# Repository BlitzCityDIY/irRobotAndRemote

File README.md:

This is for a rover robot built with the Adafruit Crickit board. 

It's controlled with an IR remote using an Adafruit Trinket M0, Adafruit Seesaw and custom PCB.

Coded with CircuitPython.

Project Videos:

https://youtu.be/yoQC8QCEBIY

https://youtu.be/6JI83SIRhTM

https://youtu.be/Heaa0BWK_Mk

https://youtu.be/sYn7sI7BDCw

Fusion 360 Public Links

Remote Main Body: https://a360.co/2XNJTZd

LED Cat Faceplate: https://a360.co/2WIM9Eo

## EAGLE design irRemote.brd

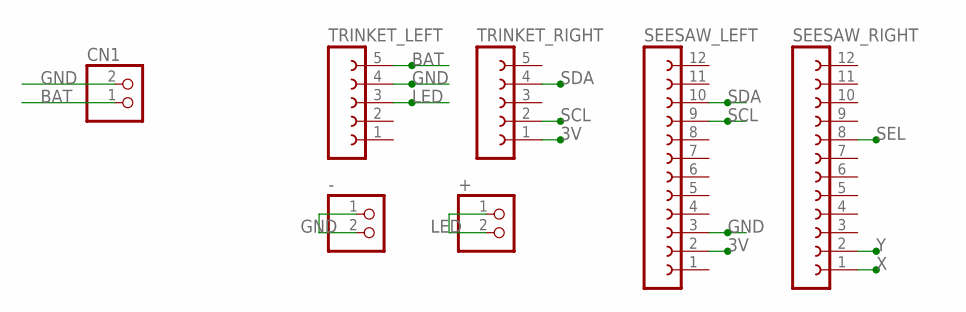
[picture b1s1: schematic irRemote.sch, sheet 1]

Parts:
+: PINHD-1X2; 1X02
-: PINHD-1X2; 1X02
CN1: JST_2PIN-SMT-RA; JST-PH-2-SMT-RA
SEESAW_LEFT: FE12-1; FE12
SEESAW_RIGHT: FE12-1; FE12
TRINKET_LEFT: FE05-1
TRINKET_RIGHT: FE05-1

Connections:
3V: SEESAW_LEFT.2, TRINKET_RIGHT.1; also elsewhere on the board
BAT: CN1.1 (2), TRINKET_LEFT.5
GND: -.1, -.2, CN1.2 (1), SEESAW_LEFT.3, TRINKET_LEFT.4; also elsewhere on the board
LED: +.1, +.2, TRINKET_LEFT.3
SCL: SEESAW_LEFT.9, TRINKET_RIGHT.2
SDA: SEESAW_LEFT.10, TRINKET_RIGHT.4
SEL: SEESAW_RIGHT.8; also elsewhere on the board
X: SEESAW_RIGHT.1; also elsewhere on the board
Y: SEESAW_RIGHT.2; also elsewhere on the board

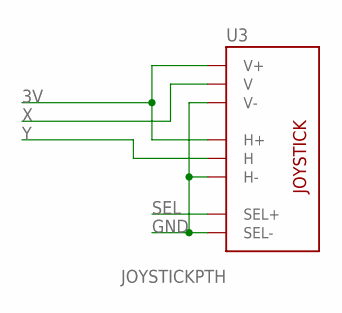
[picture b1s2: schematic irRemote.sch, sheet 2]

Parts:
U3: JOYSTICKPTH; JOYSTICK

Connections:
3V: U3.H1 (H+), U3.V1 (V+); also elsewhere on the board
GND: U3.B2A (SEL-), U3.H3 (H-), U3.V3 (V-); also elsewhere on the board
SEL: U3.B1A (SEL+); also elsewhere on the board
X: U3.V2 (V); also elsewhere on the board
Y: U3.H2 (H); also elsewhere on the board

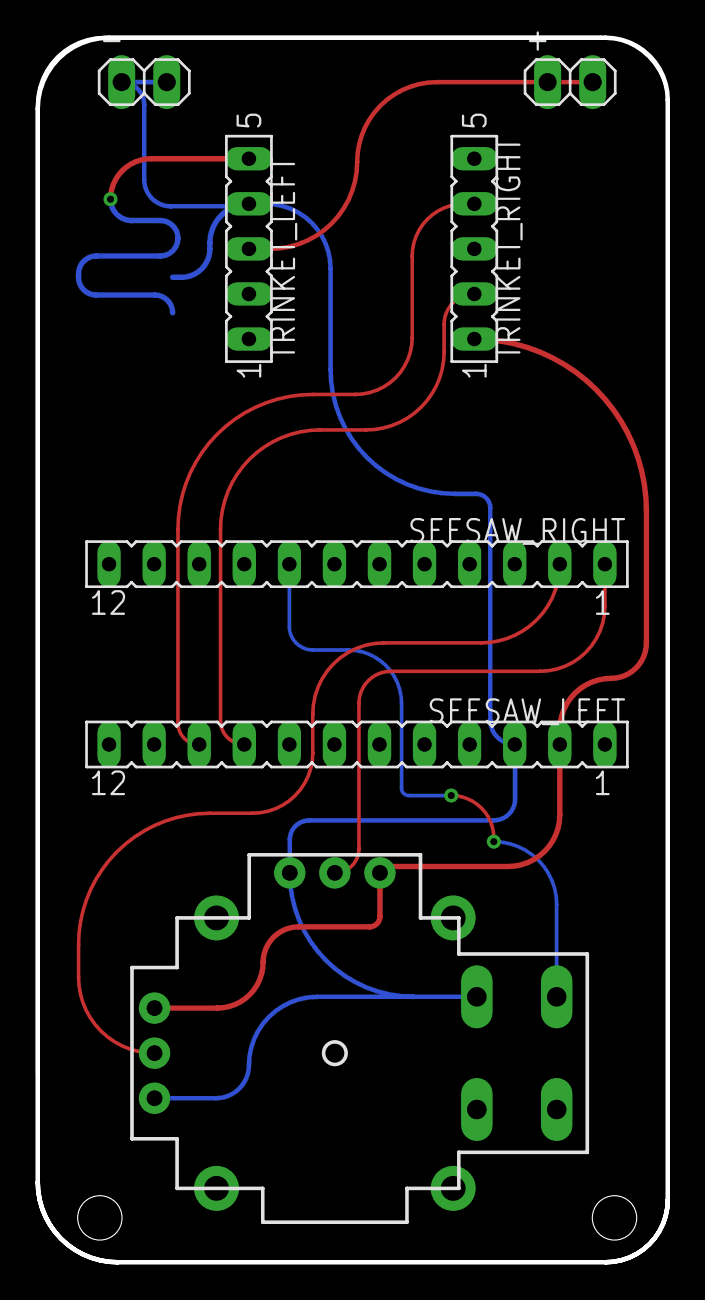
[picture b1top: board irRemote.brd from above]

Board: 2 copper layers, 35.5 x 69.0 mm, 8 parts (1 on the bottom side), 9 nets.

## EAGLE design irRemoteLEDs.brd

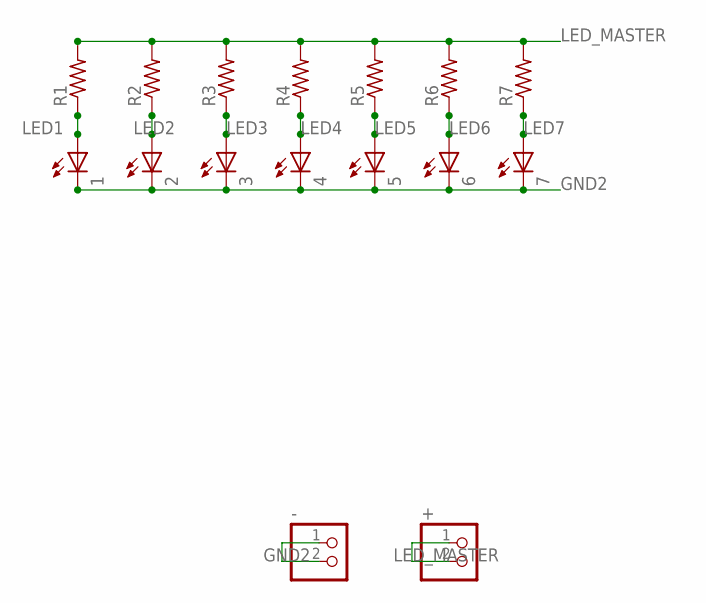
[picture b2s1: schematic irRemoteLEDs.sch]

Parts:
1, 2, 3, 4, 5, 6, 7: LED5MM
+: PINHD-1X2; 1X02
-: PINHD-1X2; 1X02
R1, R2, R3, R4, R5, R6, R7: R-US_M0805; M0805

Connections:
GND2: 1.K (C), 2.K (C), 3.K (C), 4.K (C), 5.K (C), 6.K (C), 7.K (C), -.1, -.2
LED1: 1.A, R1.1
LED2: 2.A, R2.1
LED3: 3.A, R3.1
LED4: 4.A, R4.1
LED5: 5.A, R5.1
LED6: 6.A, R6.1
LED7: 7.A, R7.1
LED_MASTER: +.1, +.2, R1.2, R2.2, R3.2, R4.2, R5.2, R6.2, R7.2

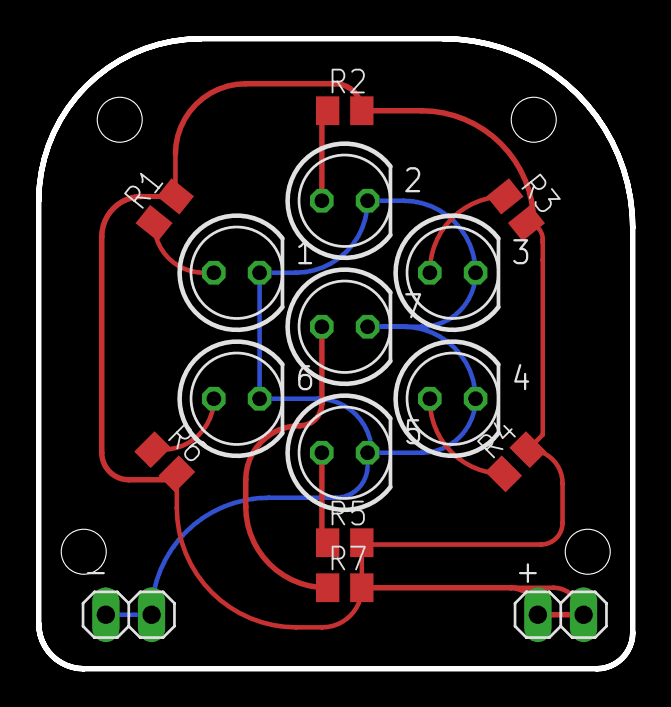
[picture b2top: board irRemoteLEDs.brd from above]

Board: 2 copper layers, 33.0 x 35.0 mm, 16 parts (0 on the bottom side), 9 nets.

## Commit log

2019-04-14 IR Robot and IR Remote CircuitPython code files
2019-06-15 Eagle files for the IR remote PCBs
    Includes schematic and board files for both the main control board and the IR LED array board that plugs in via headers
2019-06-15 Added Fusion 360 links
2019-06-15 3D .STL files
